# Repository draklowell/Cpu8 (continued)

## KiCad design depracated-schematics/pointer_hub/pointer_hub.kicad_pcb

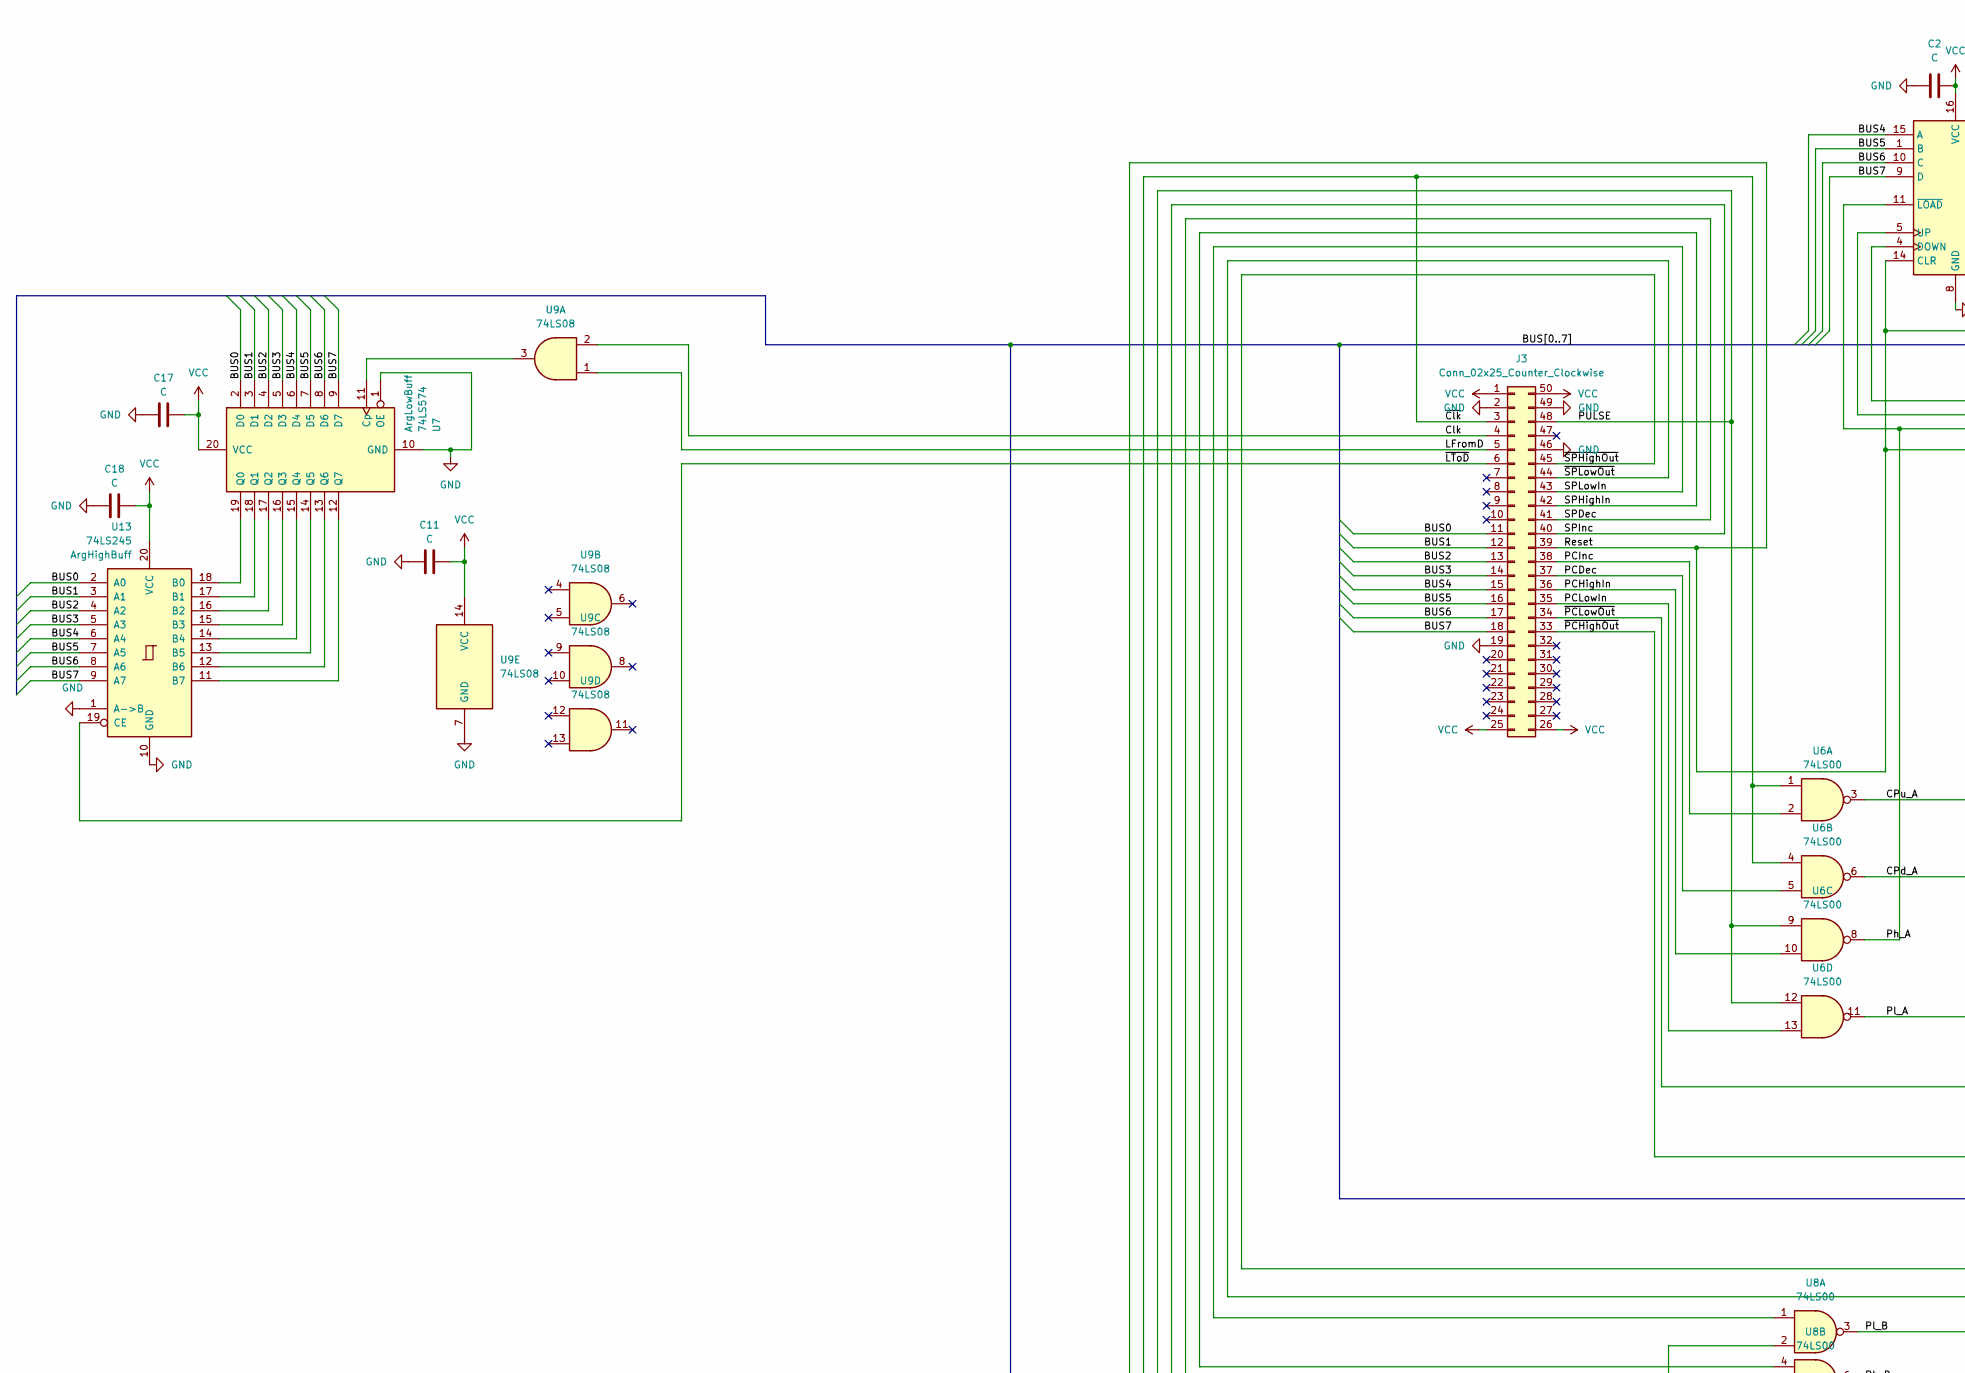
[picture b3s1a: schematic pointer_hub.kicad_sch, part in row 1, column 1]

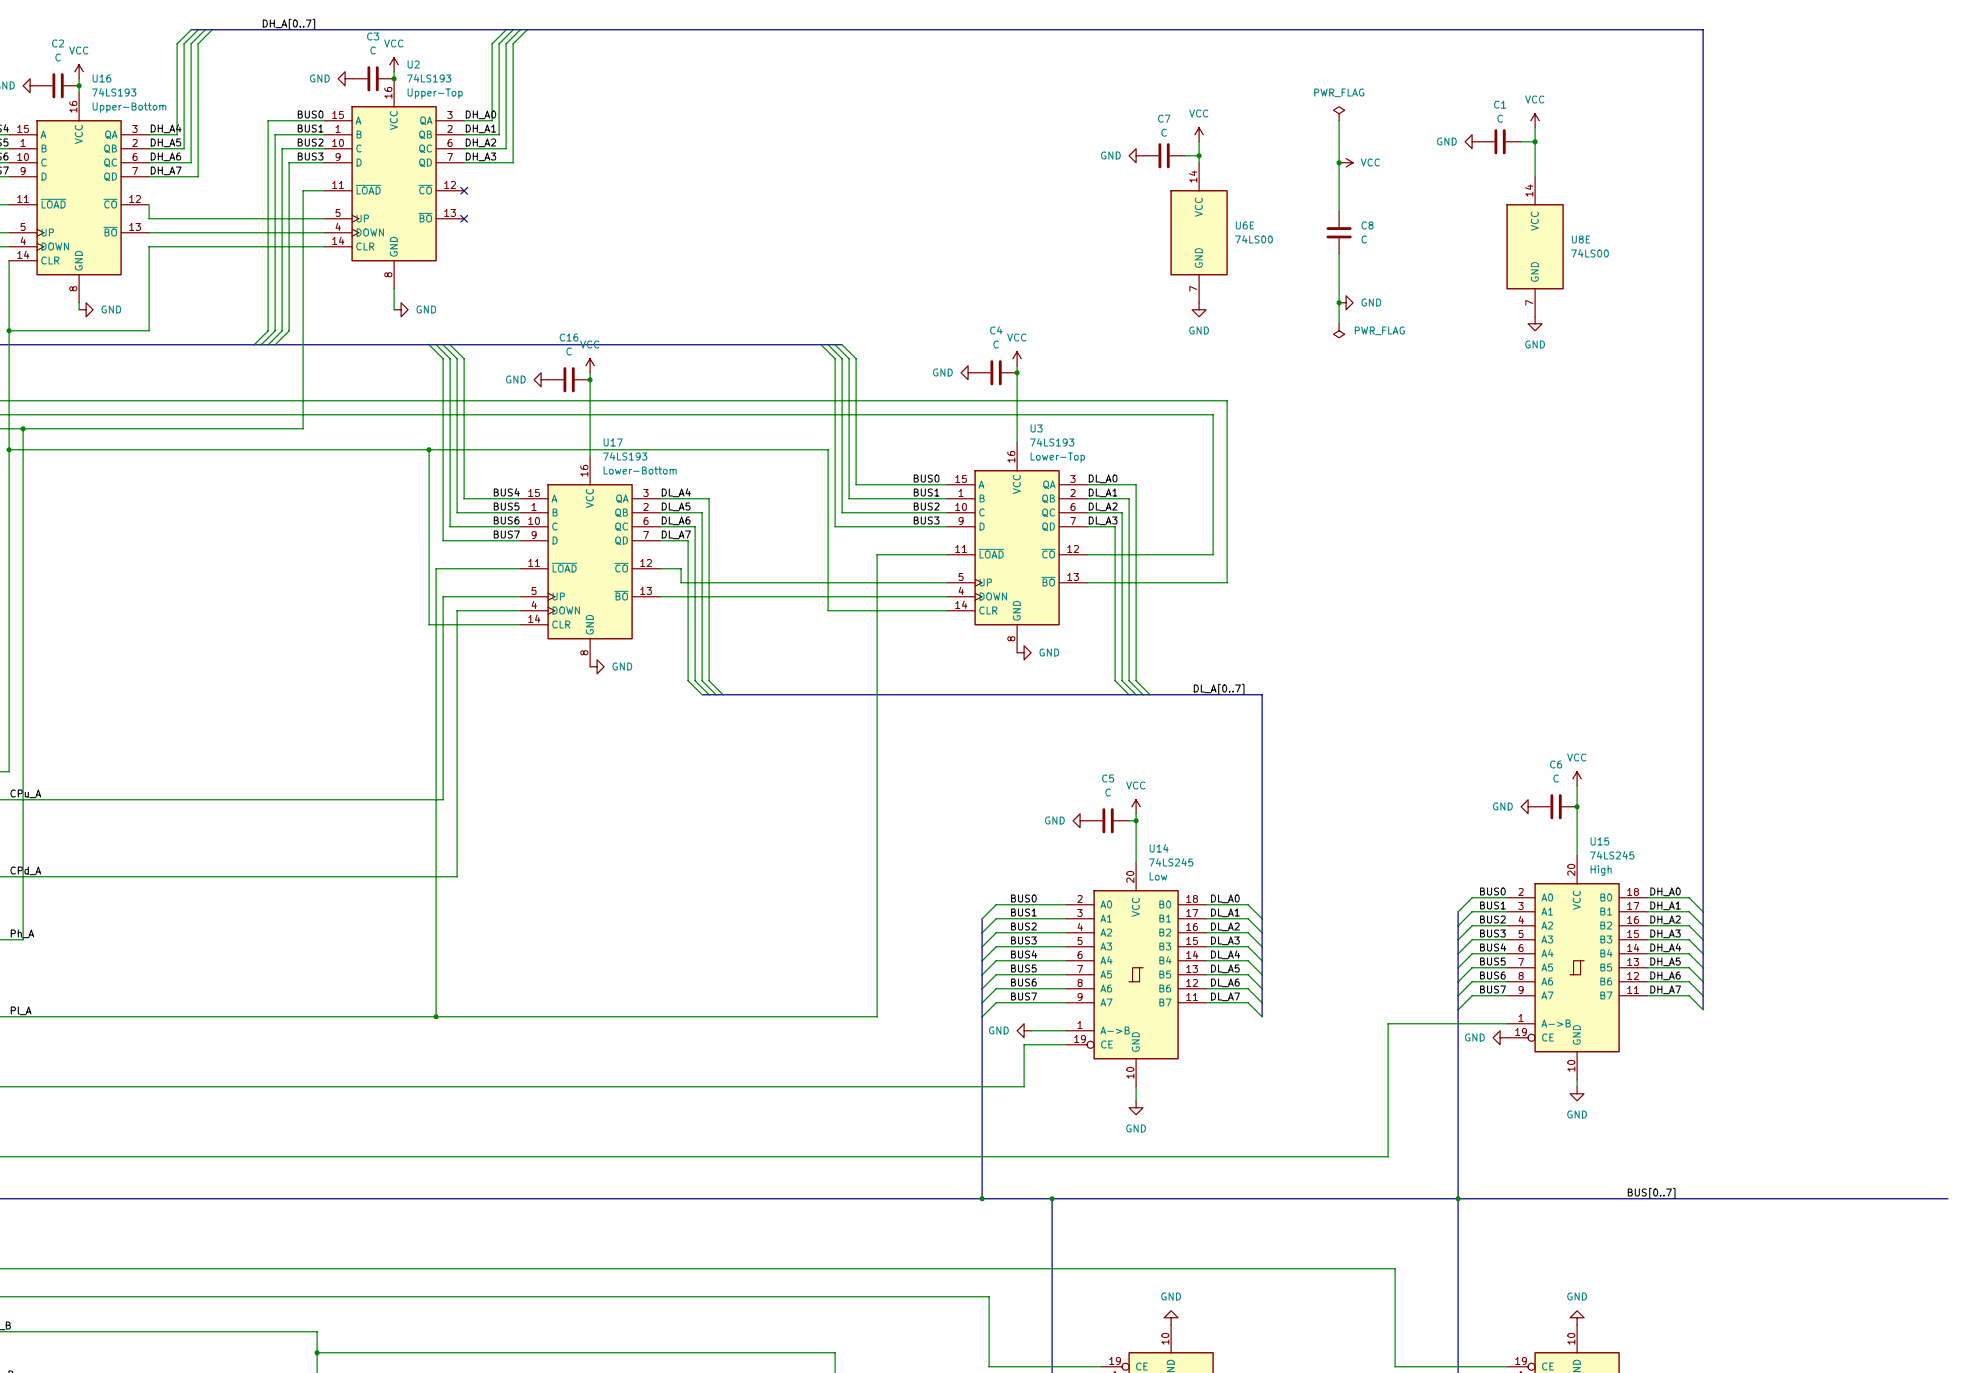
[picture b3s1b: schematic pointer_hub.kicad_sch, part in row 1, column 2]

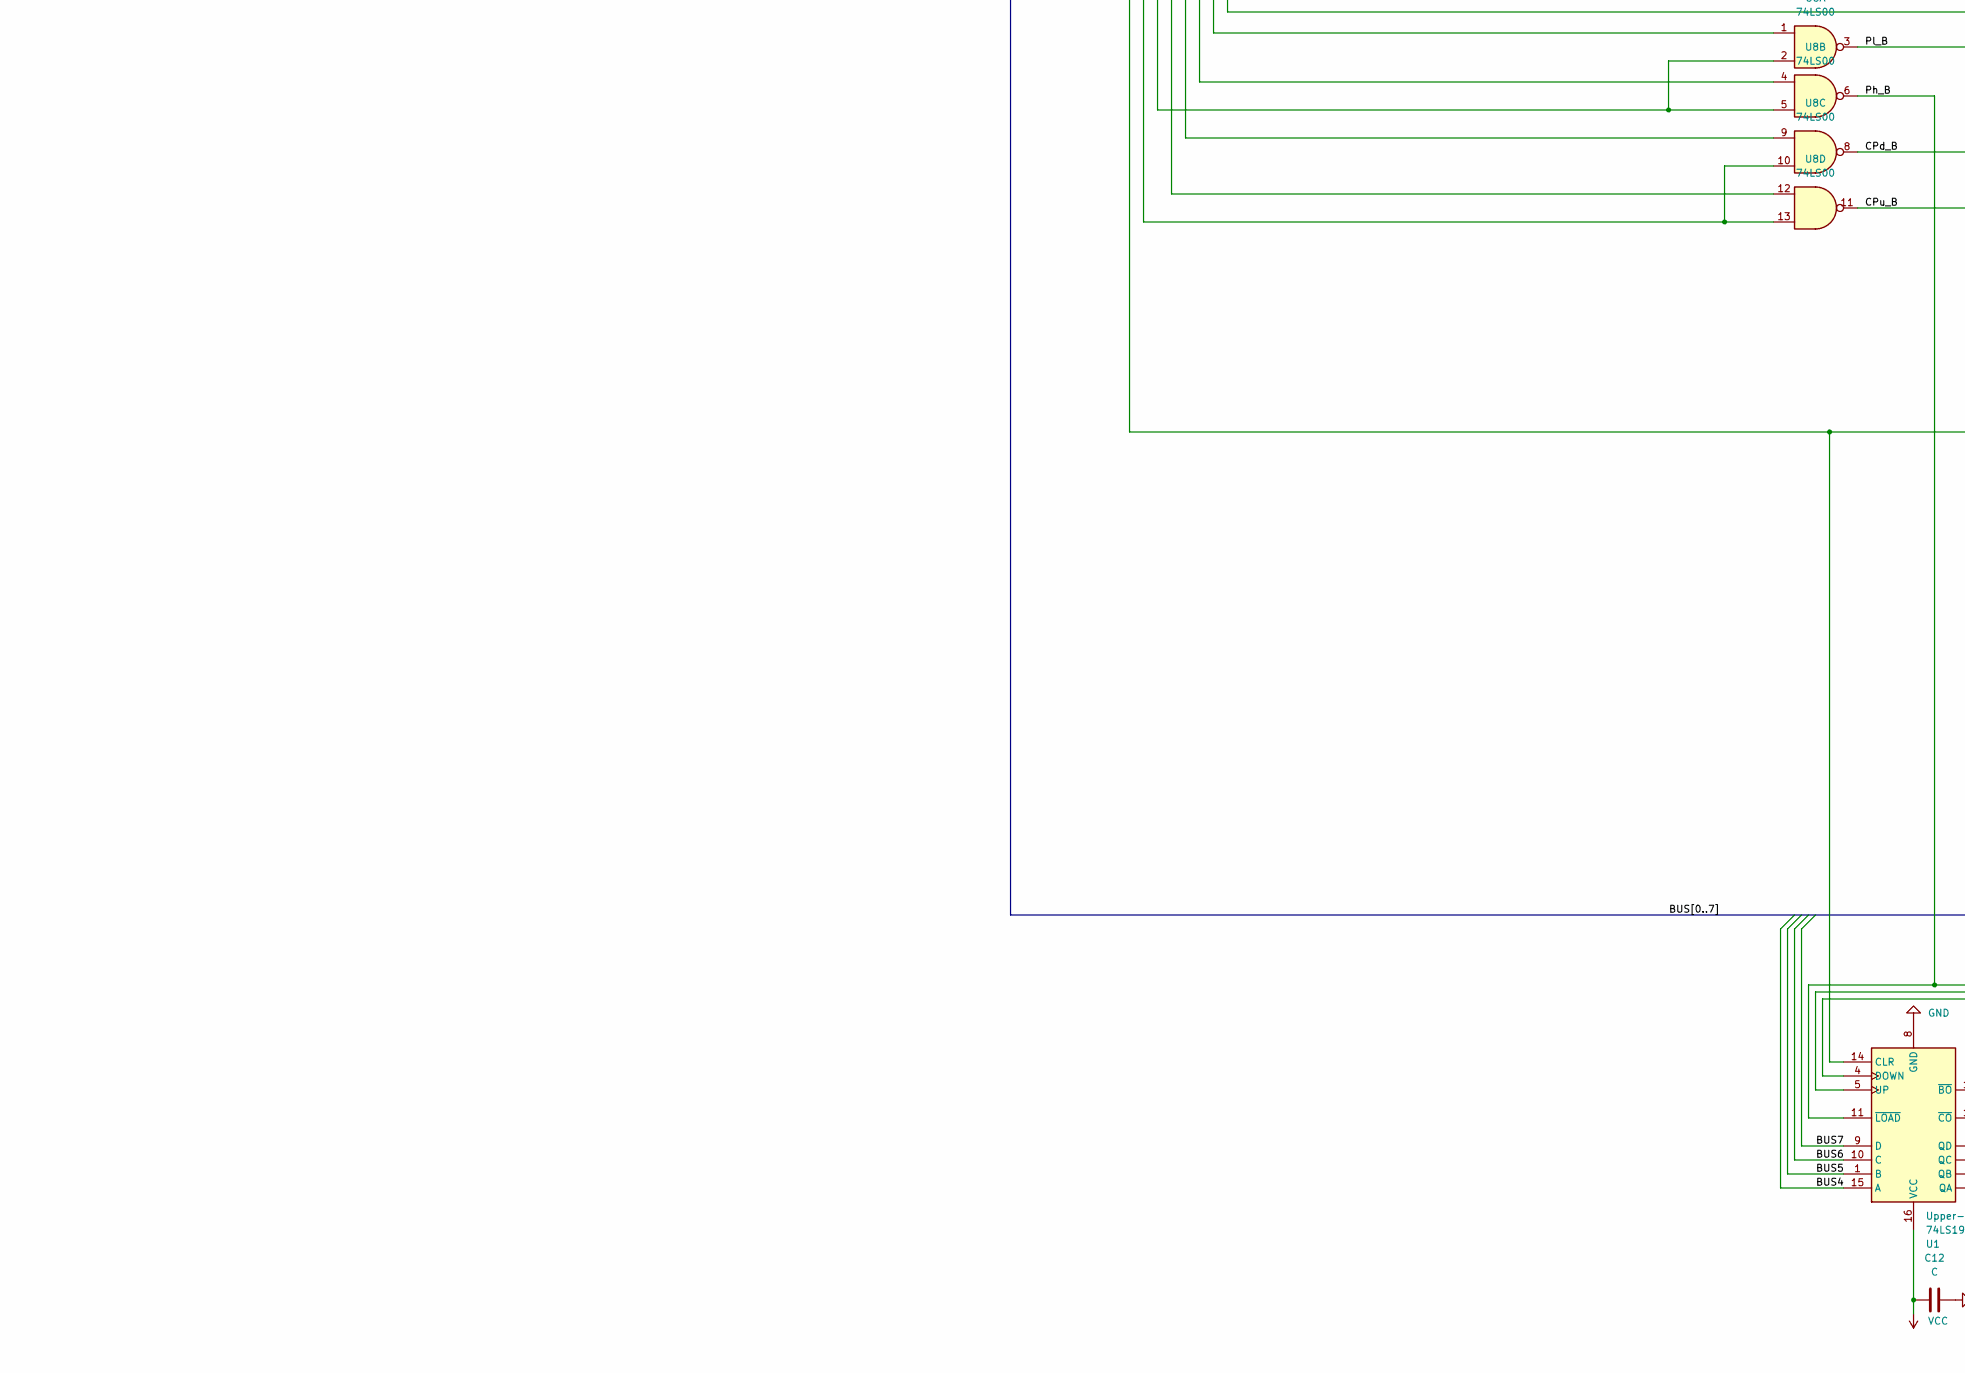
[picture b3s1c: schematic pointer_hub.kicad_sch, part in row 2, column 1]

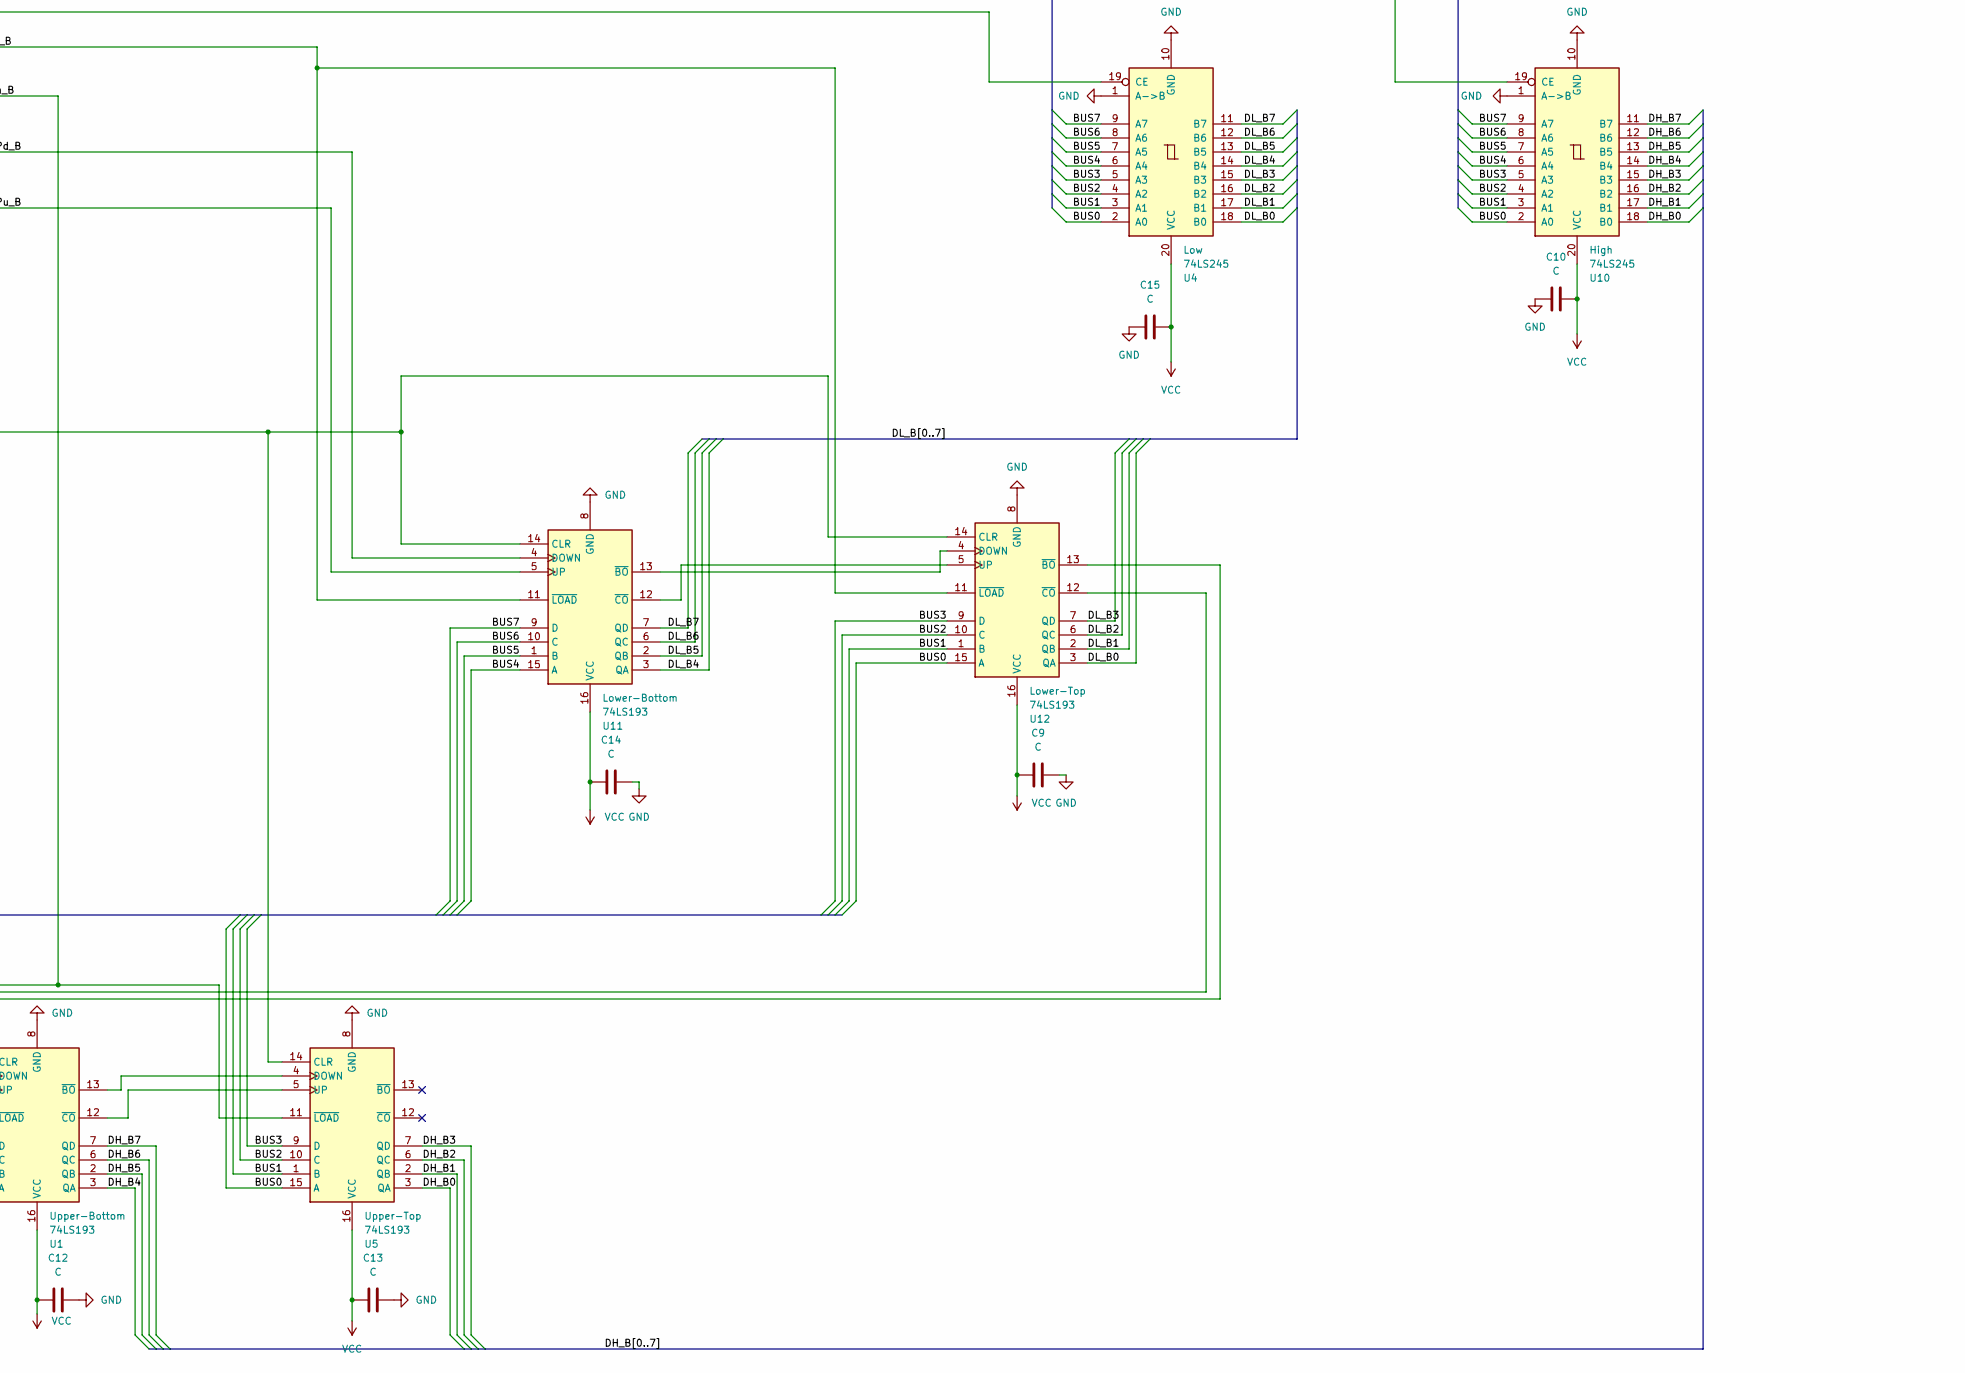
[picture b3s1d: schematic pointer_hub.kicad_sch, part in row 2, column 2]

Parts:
C1, C2, C3, C4, C5, C6, C7, C8, C9, C10, C11, C12, C13, C14, C15, C16, C17, C18: C; CP_Radial_D4.0mm_P1.50mm
J3: Conn_02x25_Counter_Clockwise; PinSocket_2x25_P2.54mm_Horizontal
U1, U2, U3, U5, U11, U12, U16, U17: 74LS193; DIP-16_W7.62mm_Socket_LongPads
U4, U10, U13, U14, U15: 74LS245; DIP-20_W7.62mm_Socket_LongPads
U6, U8: 74LS00; DIP-14_W7.62mm_Socket_LongPads
U7: 74LS574; DIP-20_W7.62mm_Socket_LongPads
U9: 74LS08; DIP-14_W7.62mm_Socket_LongPads

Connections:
/BUS0: J3.11, U2.15 (A), U3.15 (A), U4.2 (A0), U5.15 (A), U7.2 (D0), U10.2 (A0), U12.15 (A), U13.2 (A0), U14.2 (A0), U15.2 (A0)
/BUS1: J3.12, U2.1 (B), U3.1 (B), U4.3 (A1), U5.1 (B), U7.3 (D1), U10.3 (A1), U12.1 (B), U13.3 (A1), U14.3 (A1), U15.3 (A1)
/BUS2: J3.13, U2.10 (C), U3.10 (C), U4.4 (A2), U5.10 (C), U7.4 (D2), U10.4 (A2), U12.10 (C), U13.4 (A2), U14.4 (A2), U15.4 (A2)
/BUS3: J3.14, U2.9 (D), U3.9 (D), U4.5 (A3), U5.9 (D), U7.5 (D3), U10.5 (A3), U12.9 (D), U13.5 (A3), U14.5 (A3), U15.5 (A3)
/BUS4: J3.15, U1.15 (A), U4.6 (A4), U7.6 (D4), U10.6 (A4), U11.15 (A), U13.6 (A4), U14.6 (A4), U15.6 (A4), U16.15 (A), U17.15 (A)
/BUS5: J3.16, U1.1 (B), U4.7 (A5), U7.7 (D5), U10.7 (A5), U11.1 (B), U13.7 (A5), U14.7 (A5), U15.7 (A5), U16.1 (B), U17.1 (B)
/BUS6: J3.17, U1.10 (C), U4.8 (A6), U7.8 (D6), U10.8 (A6), U11.10 (C), U13.8 (A6), U14.8 (A6), U15.8 (A6), U16.10 (C), U17.10 (C)
/BUS7: J3.18, U1.9 (D), U4.9 (A7), U7.9 (D7), U10.9 (A7), U11.9 (D), U13.9 (A7), U14.9 (A7), U15.9 (A7), U16.9 (D), U17.9 (D)
/CPd_A: U6.6, U17.4 (DOWN)
/CPd_B: U8.8, U11.4 (DOWN)
/CPu_A: U6.3, U17.5 (UP)
/CPu_B: U8.11, U11.5 (UP)
/Clk: J3.4, U9.2
/DH_A0: U2.3 (QA), U15.18 (B0)
/DH_A1: U2.2 (QB), U15.17 (B1)
/DH_A2: U2.6 (QC), U15.16 (B2)
/DH_A3: U2.7 (QD), U15.15 (B3)
/DH_A4: U15.14 (B4), U16.3 (QA)
/DH_A5: U15.13 (B5), U16.2 (QB)
/DH_A6: U15.12 (B6), U16.6 (QC)
/DH_A7: U15.11 (B7), U16.7 (QD)
/DH_B0: U5.3 (QA), U10.18 (B0)
/DH_B1: U5.2 (QB), U10.17 (B1)
/DH_B2: U5.6 (QC), U10.16 (B2)
/DH_B3: U5.7 (QD), U10.15 (B3)
/DH_B4: U1.3 (QA), U10.14 (B4)
/DH_B5: U1.2 (QB), U10.13 (B5)
/DH_B6: U1.6 (QC), U10.12 (B6)
/DH_B7: U1.7 (QD), U10.11 (B7)
/DL_A0: U3.3 (QA), U14.18 (B0)
/DL_A1: U3.2 (QB), U14.17 (B1)
/DL_A2: U3.6 (QC), U14.16 (B2)
/DL_A3: U3.7 (QD), U14.15 (B3)
/DL_A4: U14.14 (B4), U17.3 (QA)
/DL_A5: U14.13 (B5), U17.2 (QB)
/DL_A6: U14.12 (B6), U17.6 (QC)
/DL_A7: U14.11 (B7), U17.7 (QD)
/DL_B0: U4.18 (B0), U12.3 (QA)
/DL_B1: U4.17 (B1), U12.2 (QB)
/DL_B2: U4.16 (B2), U12.6 (QC)
/DL_B3: U4.15 (B3), U12.7 (QD)
/DL_B4: U4.14 (B4), U11.3 (QA)
/DL_B5: U4.13 (B5), U11.2 (QB)
/DL_B6: U4.12 (B6), U11.6 (QC)
/DL_B7: U4.11 (B7), U11.7 (QD)
/LFromD: J3.5, U9.1
/PCDec: J3.37, U6.5
/PCHighIn: J3.36, U6.10
/PCInc: J3.38, U6.2
/PCLowIn: J3.35, U6.13
/PULSE: J3.48, U6.9, U6.12, U8.2, U8.5
/Ph_A: U2.11 (~LOAD), U6.8, U16.11 (~LOAD)
/Ph_B: U1.11 (~LOAD), U5.11 (~LOAD), U8.6
/Pl_A: U3.11 (~LOAD), U6.11, U17.11 (~LOAD)
/Pl_B: U8.3, U11.11 (~LOAD), U12.11 (~LOAD)
/Reset: J3.39, U1.14 (CLR), U2.14 (CLR), U3.14 (CLR), U5.14 (CLR), U11.14 (CLR), U12.14 (CLR), U16.14 (CLR), U17.14 (CLR)
/SPDec: J3.41, U8.9
/SPHighIn: J3.42, U8.4
/SPInc: J3.40, U8.12
/SPLowIn: J3.43, U8.1
/~Clk: J3.3, U6.1, U6.4, U8.10, U8.13
/~LToD: J3.6, U13.19 (CE)
/~PСHighOut: J3.33, U15.1 (A->B)
/~PСLowOut: J3.34, U14.19 (CE)
/~SPHighOut: J3.45, U10.19 (CE)
/~SPLowOut: J3.44, U4.19 (CE)
GND: C1.1, C2.1, C3.1, C4.1, C5.2, C6.2, C7.1, C8.2, C9.1, C10.1, C11.1, C12.1, C13.1, C14.1, C15.1, C16.1, C17.1, C18.1, J3.2, J3.19, J3.46, J3.49, U1.8 (GND), U2.8 (GND), U3.8 (GND), U4.1 (A->B), U4.10 (GND), U5.8 (GND), U6.7 (GND), U7.1 (OE), U7.10 (GND), U8.7 (GND), U9.7 (GND), U10.1 (A->B), U10.10 (GND), U11.8 (GND), U12.8 (GND), U13.1 (A->B), U13.10 (GND), U14.1 (A->B), U14.10 (GND), U15.10 (GND), U15.19 (CE), U16.8 (GND), U17.8 (GND)
unnamed: U1.4 (DOWN), U12.13 (~BO)
unnamed: U1.5 (UP), U12.12 (~CO)
unnamed: U1.13 (~BO), U5.4 (DOWN)
unnamed: U1.12 (~CO), U5.5 (UP)
unnamed: U7.11 (Cp), U9.3
unnamed: U11.13 (~BO), U12.4 (DOWN)
unnamed: U11.12 (~CO), U12.5 (UP)
unnamed: U7.19 (Q0), U13.18 (B0)
unnamed: U7.18 (Q1), U13.17 (B1)
unnamed: U7.17 (Q2), U13.16 (B2)
unnamed: U7.16 (Q3), U13.15 (B3)
unnamed: U7.15 (Q4), U13.14 (B4)
unnamed: U7.14 (Q5), U13.13 (B5)
unnamed: U7.13 (Q6), U13.12 (B6)
unnamed: U7.12 (Q7), U13.11 (B7)
unnamed: U3.13 (~BO), U16.4 (DOWN)
unnamed: U3.12 (~CO), U16.5 (UP)
unnamed: U2.4 (DOWN), U16.13 (~BO)
unnamed: U2.5 (UP), U16.12 (~CO)
unnamed: U3.4 (DOWN), U17.13 (~BO)
unnamed: U3.5 (UP), U17.12 (~CO)
VCC: C1.2, C2.2, C3.2, C4.2, C5.1, C6.1, C7.2, C8.1, C9.2, C10.2, C11.2, C12.2, C13.2, C14.2, C15.2, C16.2, C17.2, C18.2, J3.1, J3.25, J3.26, J3.50, U1.16 (VCC), U2.16 (VCC), U3.16 (VCC), U4.20 (VCC), U5.16 (VCC), U6.14 (VCC), U7.20 (VCC), U8.14 (VCC), U9.14 (VCC), U10.20 (VCC), U11.16 (VCC), U12.16 (VCC), U13.20 (VCC), U14.20 (VCC), U15.20 (VCC), U16.16 (VCC), U17.16 (VCC)

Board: 2 copper layers, 36 parts (0 on the bottom side), 89 nets, no tracks yet.

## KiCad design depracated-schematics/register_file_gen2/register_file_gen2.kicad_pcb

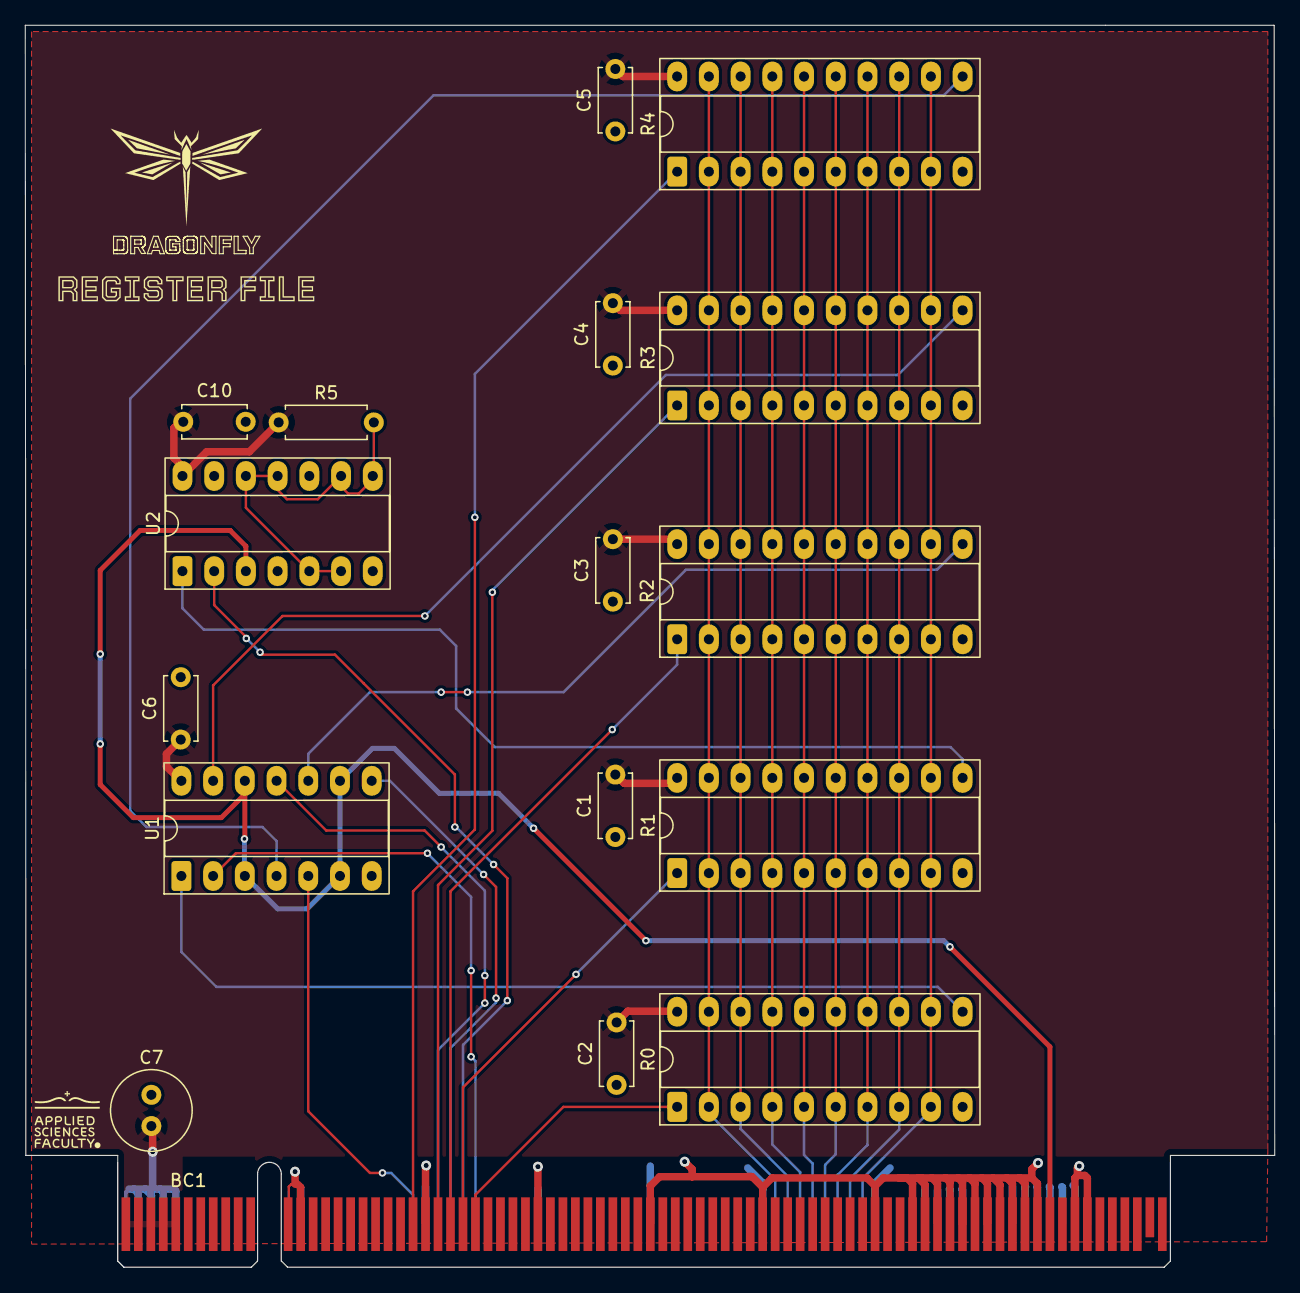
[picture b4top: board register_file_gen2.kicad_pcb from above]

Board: 2 copper layers, 100.0 x 99.5 mm, 18 parts (0 on the bottom side), 27 nets.

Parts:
BC1: BusConnector; BUS_PCIexpress_x16
C1, C2, C3, C4, C5, C6, C10: C; C_Disc_D5.0mm_W2.5mm_P5.00mm
C7: C; C_Radial_D6.3mm_H5.0mm_P2.50mm
R0, R1, R2, R3, R4: 74LS574; DIP-20_W7.62mm_Socket_LongPads
R5: R; R_Axial_DIN0207_L6.3mm_D2.5mm_P7.62mm_Horizontal
U1, U2: 74LS02; DIP-14_W7.62mm_Socket_LongPads
kibuzzard-6911B41A: G***; kibuzzard-6911B41A

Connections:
/D0: BC1.A51 (DATA0), R0.2 (D0), R0.19 (Q0), R1.2 (D0), R1.19 (Q0), R2.2 (D0), R2.19 (Q0), R3.2 (D0), R3.19 (Q0), R4.2 (D0), R4.19 (Q0)
/D1: BC1.A52 (DATA1), R0.3 (D1), R0.18 (Q1), R1.3 (D1), R1.18 (Q1), R2.3 (D1), R2.18 (Q1), R3.3 (D1), R3.18 (Q1), R4.3 (D1), R4.18 (Q1)
/D2: BC1.A53 (DATA2), R0.4 (D2), R0.17 (Q2), R1.4 (D2), R1.17 (Q2), R2.4 (D2), R2.17 (Q2), R3.4 (D2), R3.17 (Q2), R4.4 (D2), R4.17 (Q2)
/D3: BC1.A54 (DATA3), R0.5 (D3), R0.16 (Q3), R1.5 (D3), R1.16 (Q3), R2.5 (D3), R2.16 (Q3), R3.5 (D3), R3.16 (Q3), R4.5 (D3), R4.16 (Q3)
/D4: BC1.A55 (DATA4), R0.6 (D4), R0.15 (Q4), R1.6 (D4), R1.15 (Q4), R2.6 (D4), R2.15 (Q4), R3.6 (D4), R3.15 (Q4), R4.6 (D4), R4.15 (Q4)
/D5: BC1.A56 (DATA5), R0.7 (D5), R0.14 (Q5), R1.7 (D5), R1.14 (Q5), R2.7 (D5), R2.14 (Q5), R3.7 (D5), R3.14 (Q5), R4.7 (D5), R4.14 (Q5)
/D6: BC1.A57 (DATA6), R0.8 (D6), R0.13 (Q6), R1.8 (D6), R1.13 (Q6), R2.8 (D6), R2.13 (Q6), R3.8 (D6), R3.13 (Q6), R4.8 (D6), R4.13 (Q6)
/D7: BC1.A58 (DATA7), R0.9 (D7), R0.12 (Q7), R1.9 (D7), R1.12 (Q7), R2.9 (D7), R2.12 (Q7), R3.9 (D7), R3.12 (Q7), R4.9 (D7), R4.12 (Q7)
GND: BC1.A12 (GND), BC1.A13 (GND), BC1.A23 (GND), BC1.A32 (GND), BC1.A41 (GND), BC1.A50 (GND), BC1.A59 (GND), BC1.A63 (GND), BC1.A64 (GND), BC1.A65 (GND), BC1.A66 (GND), BC1.A70 (GND), BC1.A71 (GND), BC1.A72 (GND), BC1.A73 (GND), BC1.A74 (GND), BC1.A75 (GND), BC1.A76 (GND), BC1.B12 (GND), BC1.B13 (GND), BC1.B23 (GND), BC1.B32 (GND), BC1.B41 (GND), BC1.B50 (GND), BC1.B59 (GND), BC1.B62 (GND), BC1.B63 (GND), BC1.B64 (GND), BC1.B65 (GND), BC1.B66 (GND), BC1.B67 (GND), BC1.B68 (GND), BC1.B69 (GND), BC1.B70 (GND), BC1.B71 (GND), BC1.B72 (GND), BC1.B75 (GND), BC1.B76 (GND), C1.1, C2.1, C3.1, C4.1, C5.1, C6.2, C7.2, C10.2, R0.10 (GND), R1.10 (GND), R2.10 (GND), R3.10 (GND), R4.10 (GND), U1.7 (GND), U2.7 (GND)
unnamed: BC1.B73 (~CLK), U1.3, U1.6, U1.9, U1.12, U2.3
unnamed: BC1.A22 (~LXH), U1.5
unnamed: BC1.A25 (~LYH), U1.8
unnamed: BC1.A24 (~LYL), U1.11
unnamed: BC1.A27 (~LZH), U1.2
unnamed: BC1.A26 (~LZL), U2.2
unnamed: BC1.B22 (~RXH), R4.1 (OE)
unnamed: BC1.B25 (~RYH), R2.1 (OE)
unnamed: BC1.B24 (~RYL), R3.1 (OE)
unnamed: BC1.B27 (~RZH), R0.1 (OE)
unnamed: BC1.B26 (~RZL), R1.1 (OE)
unnamed: R0.11 (Cp), U1.1
unnamed: R1.11 (Cp), U2.1
unnamed: R2.11 (Cp), U1.10
unnamed: R3.11 (Cp), U1.13
unnamed: R4.11 (Cp), U1.4
unnamed: R5.2, U2.5, U2.6, U2.8, U2.9, U2.11, U2.12
VCC: BC1.A1 (VCC), BC1.A2 (VCC), BC1.A3 (VCC), BC1.A4 (VCC), BC1.A5 (VCC), BC1.B1 (VCC), BC1.B2 (VCC), BC1.B3 (VCC), BC1.B4 (VCC), BC1.B5 (VCC), C1.2, C2.2, C3.2, C4.2, C5.2, C6.1, C7.1, C10.1, R0.20 (VCC), R1.20 (VCC), R2.20 (VCC), R3.20 (VCC), R4.20 (VCC), R5.1, U1.14 (VCC), U2.14 (VCC)

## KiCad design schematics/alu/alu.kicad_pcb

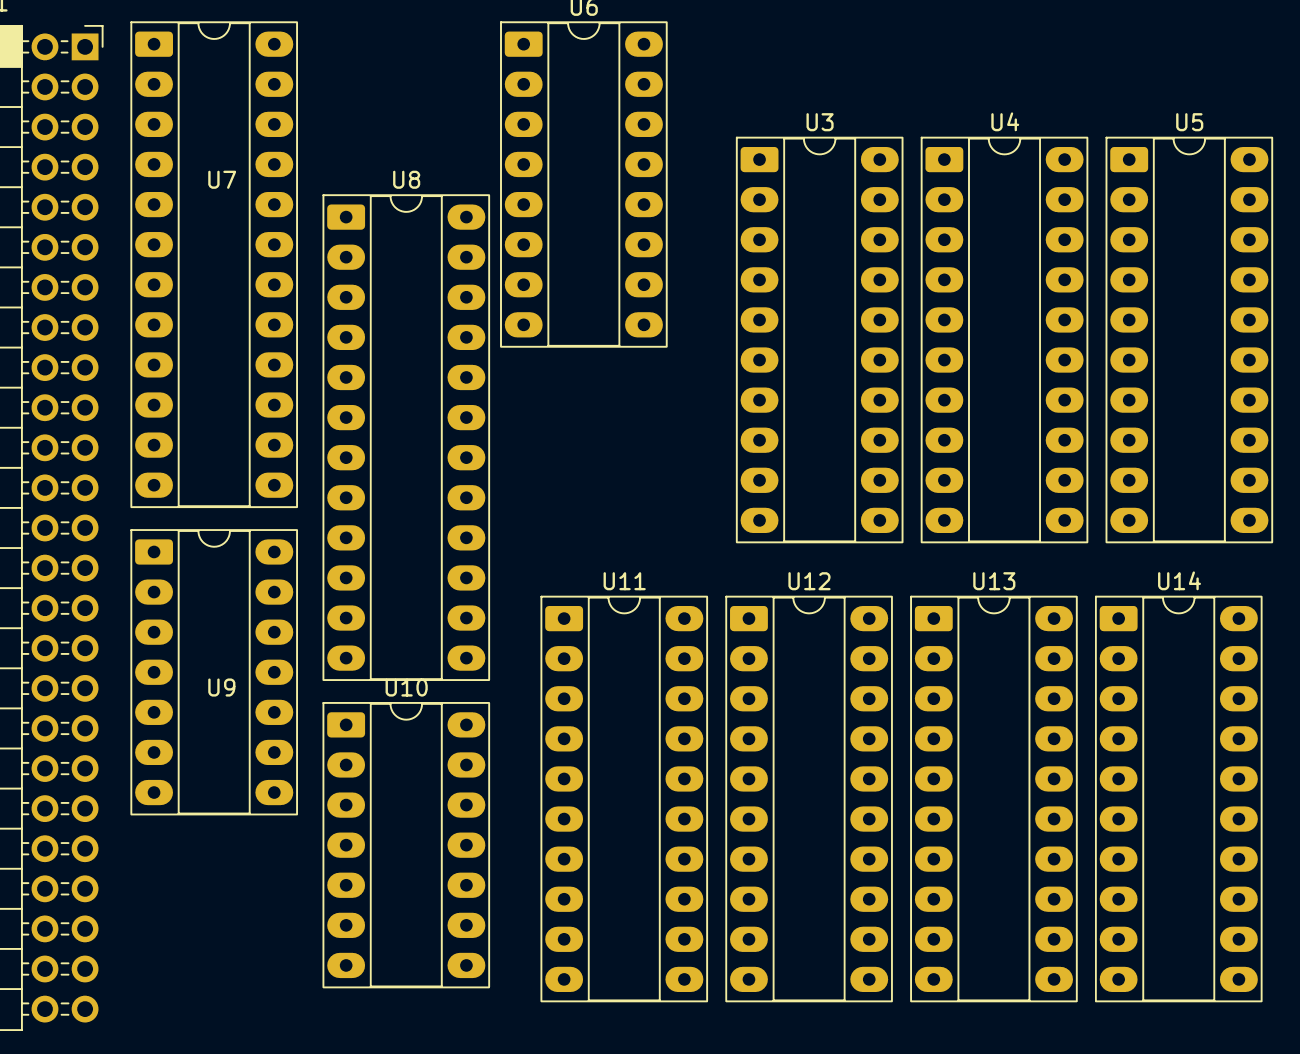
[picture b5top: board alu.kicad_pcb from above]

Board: 2 copper layers, 13 parts (0 on the bottom side), 58 nets, no tracks yet.

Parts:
J1: Conn_02x25_Counter_Clockwise; PinSocket_2x25_P2.54mm_Horizontal
U3, U4, U5, U11, U13: 74LS245; DIP-20_W7.62mm_Socket_LongPads
U6: 74LS137; DIP-16_W7.62mm_Socket_LongPads
U7, U8: 74LS181; DIP-24_W7.62mm_Socket_LongPads
U9, U10: 74LS02; DIP-14_W7.62mm_Socket_LongPads
U12, U14: 74LS574; DIP-20_W7.62mm_Socket_LongPads

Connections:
/ACCUM0: U4.3 (A1), U5.2 (A0), U7.1 (B0), U14.19 (Q0)
/ACCUM1: U3.2 (A0), U4.4 (A2), U5.3 (A1), U7.22 (B1), U14.18 (Q1)
/ACCUM2: U3.3 (A1), U4.5 (A3), U5.4 (A2), U7.20 (B2), U14.17 (Q2)
/ACCUM3: U3.4 (A2), U4.6 (A4), U5.5 (A3), U7.18 (B3), U14.16 (Q3)
/ACCUM4: U3.5 (A3), U4.7 (A5), U5.6 (A4), U8.1 (B0), U14.15 (Q4)
/ACCUM5: U3.6 (A4), U4.8 (A6), U5.7 (A5), U8.22 (B1), U14.14 (Q5)
/ACCUM6: U3.7 (A5), U4.9 (A7), U5.8 (A6), U8.20 (B2), U14.13 (Q6)
/ACCUM7: U3.8 (A6), U5.9 (A7), U8.18 (B3), U14.12 (Q7)
/BUS0: J1.11, U3.18 (B0), U4.18 (B0), U5.18 (B0), U11.2 (A0), U12.2 (D0), U13.2 (A0), U14.2 (D0)
/BUS1: J1.12, U3.17 (B1), U4.17 (B1), U5.17 (B1), U11.3 (A1), U12.3 (D1), U13.3 (A1), U14.3 (D1)
/BUS2: J1.13, U3.16 (B2), U4.16 (B2), U5.16 (B2), U11.4 (A2), U12.4 (D2), U13.4 (A2), U14.4 (D2)
/BUS3: J1.14, U3.15 (B3), U4.15 (B3), U5.15 (B3), U11.5 (A3), U12.5 (D3), U13.5 (A3), U14.5 (D3)
/BUS4: J1.15, U3.14 (B4), U4.14 (B4), U5.14 (B4), U11.6 (A4), U12.6 (D4), U13.6 (A4), U14.6 (D4)
/BUS5: J1.16, U3.13 (B5), U4.13 (B5), U5.13 (B5), U11.7 (A5), U12.7 (D5), U13.7 (A5), U14.7 (D5)
/BUS6: J1.17, U3.12 (B6), U4.12 (B6), U5.12 (B6), U11.8 (A6), U12.8 (D6), U13.8 (A6), U14.8 (D6)
/BUS7: J1.18, U3.11 (B7), U4.11 (B7), U5.11 (B7), U11.9 (A7), U12.9 (D7), U13.9 (A7), U14.9 (D7)
/H0: U7.2 (A0), U12.19 (Q0), U13.18 (B0)
/H1: U7.23 (A1), U12.18 (Q1), U13.17 (B1)
/H2: U7.21 (A2), U12.17 (Q2), U13.16 (B2)
/H3: U7.19 (A3), U12.16 (Q3), U13.15 (B3)
/H4: U8.2 (A0), U12.15 (Q4), U13.14 (B4)
/H5: U8.23 (A1), U12.14 (Q5), U13.13 (B5)
/H6: U8.21 (A2), U12.13 (Q6), U13.12 (B6)
/H7: U8.19 (A3), U12.12 (Q7), U13.11 (B7)
/MODE: J1.31, U7.8 (M), U8.8 (M)
/S0: J1.35, U7.6 (S0), U8.6 (S0)
/S1: J1.34, U7.5 (S1), U8.5 (S1)
/S2: J1.33, U7.4 (S2), U8.4 (S2)
/S3: J1.32, U7.3 (S3), U8.3 (S3)
/SHL: J1.29, U6.1 (A0)
/SHR: J1.28, U6.2 (A1)
/Sign: J1.38, U8.13 (F3), U9.12, U11.11 (B7)
/Zero: J1.36, U10.1
/~CARRY: J1.30, U7.7 (Cn)
/~CarryOut: J1.37, U8.16 (Cn+4)
/~Enable: J1.39, U11.19 (CE)
/~HToD: J1.41, U13.19 (CE)
/~ToD: J1.27, U6.3 (A2)
GND: J1.2, J1.10, J1.19, J1.49, U3.9 (A7), U3.10 (GND), U4.2 (A0), U4.10 (GND), U5.10 (GND), U6.4 (~GL), U6.5 (~G2), U6.8 (GND), U7.12 (GND), U8.12 (GND), U9.7 (GND), U10.7 (GND), U11.1 (A->B), U11.10 (GND), U12.1 (OE), U12.10 (GND), U13.1 (A->B), U13.10 (GND), U14.1 (OE), U14.10 (GND)
unnamed: U3.19 (CE), U6.13 (Y2)
unnamed: U4.19 (CE), U6.14 (Y1)
unnamed: U5.19 (CE), U6.15 (Y0)
unnamed: U7.16 (Cn+4), U8.7 (Cn)
unnamed: U9.1, U9.8
unnamed: U9.4, U9.9
unnamed: U9.13, U10.6
unnamed: U10.5, U10.10
unnamed: U10.4, U10.11
unnamed: U9.10, U10.12
unnamed: U10.2, U10.3, U10.13
unnamed: U7.9 (F0), U9.2, U11.18 (B0)
unnamed: U7.10 (F1), U9.3, U11.17 (B1)
unnamed: U7.11 (F2), U9.5, U11.16 (B2)
unnamed: U7.13 (F3), U9.6, U11.15 (B3)
unnamed: U8.9 (F0), U10.8, U11.14 (B4)
unnamed: U8.10 (F1), U10.9, U11.13 (B5)
unnamed: U8.11 (F2), U9.11, U11.12 (B6)
VCC: J1.1, J1.25, J1.26, J1.50, U3.20 (VCC), U4.20 (VCC), U5.20 (VCC), U6.16 (VCC), U7.24 (VCC), U8.24 (VCC), U9.14 (VCC), U10.14 (VCC), U11.20 (VCC), U12.20 (VCC), U13.20 (VCC), U14.20 (VCC)
